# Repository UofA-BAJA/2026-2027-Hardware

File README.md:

# 2026-2027-Hardware

The repository of all hardware for 2026-2027 UofA Baja

Electrical Lead - Graham VanDerBeek

Software Lead - Karsten Yin

#### Projects:

Tachometer -

Speedometer -

Shock Displacement -

Brake Pressure -

GPS -

CVT Temp -

IMU -

Dash - Adam Esch
 HELLO

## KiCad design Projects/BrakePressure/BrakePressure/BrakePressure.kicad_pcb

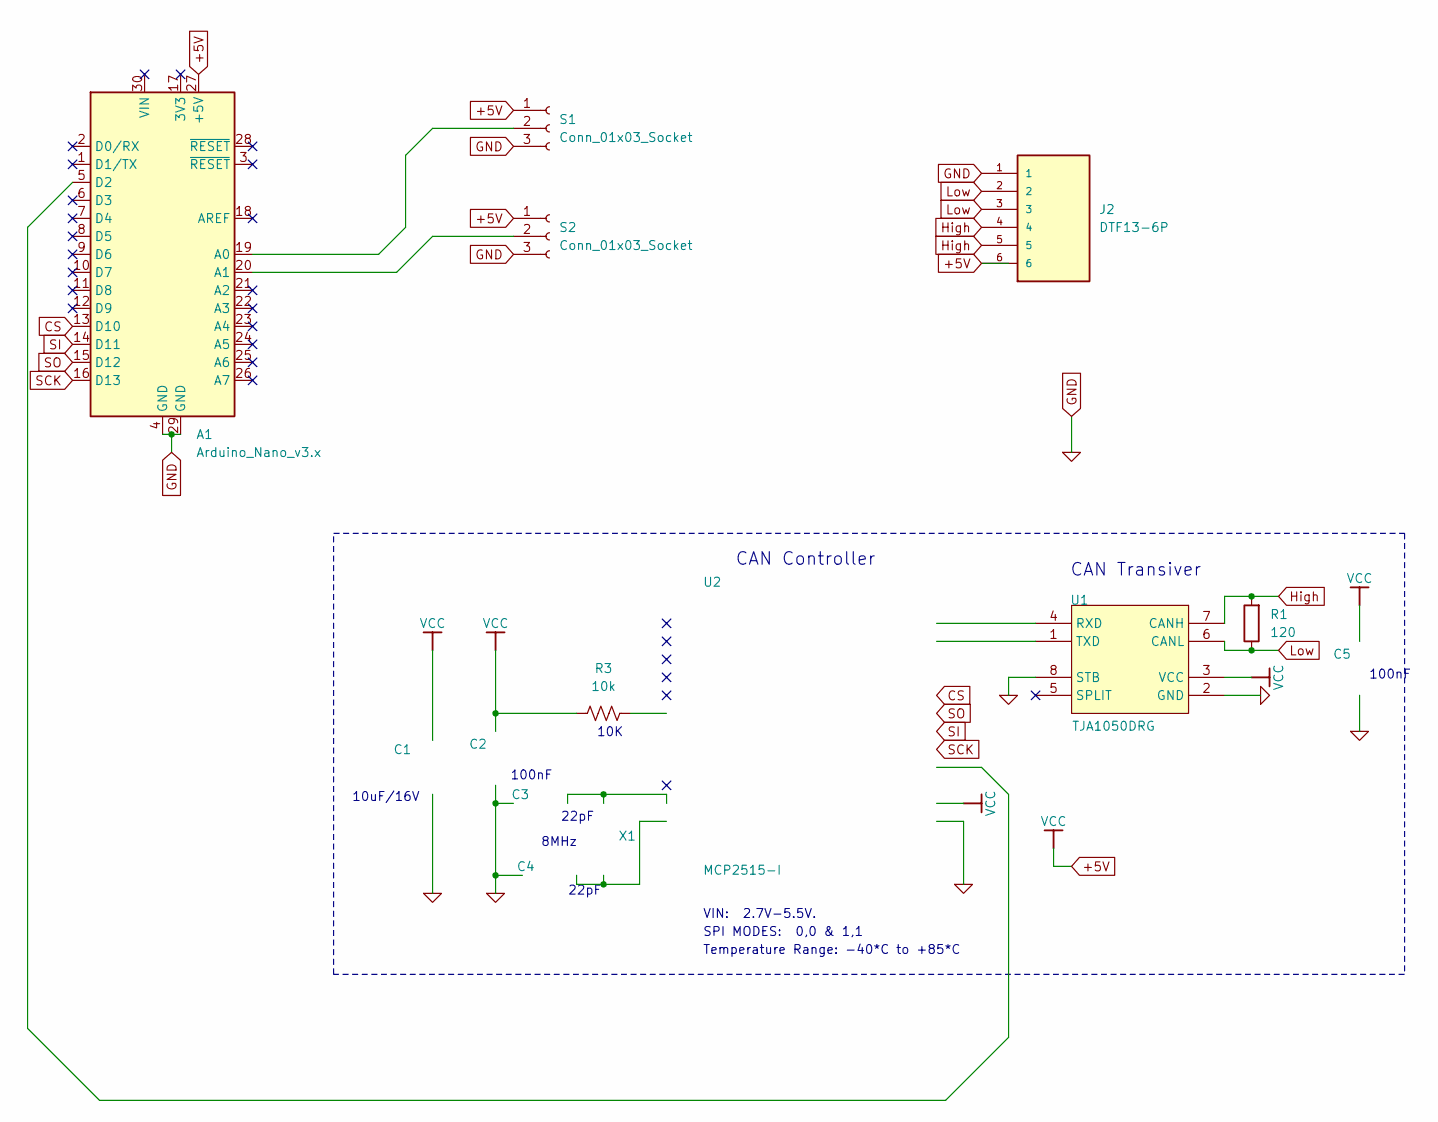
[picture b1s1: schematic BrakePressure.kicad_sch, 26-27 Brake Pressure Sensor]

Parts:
A1: Arduino_Nano_v3.x; Arduino_Nano
C1: 10uF/16V; CP_Radial_Tantal_D5.0mm_P2.50mm
C2, C5: 100nF; CP_Radial_D5.0mm_P2.50mm; PART NUMBER C0603-N.C.
C3, C4: 22pF; CP_Radial_D5.0mm_P2.50mm; PART NUMBER C0603-N.C.
J2: DTF13-6P; TE_DTF13-6P; PARTREV B
R1: 120; R_Axial_DIN0204_L3.6mm_D1.6mm_P7.62mm_Horizontal
R3: 10k; R_Axial_DIN0204_L3.6mm_D1.6mm_P7.62mm_Horizontal
S1, S2: Conn_01x03_Socket; TO-3P-3_Vertical
U1: TJA1050DRG; SOIC-8_5.3x5.3mm_P1.27mm; MANUFACTURER PART TJA1050DRG; LCSC PART NAME TJA1050DRG
U2: MCP2515-I; SOIC-18W_7.5x11.6mm_P1.27mm; MANUFACTURER PART MCP2515-I; JLCPCB PART CLASS Extended Part
X1: 8MHz; Crystal_SMD_HC49-SD

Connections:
+5V: A1.27 (+5V), C1.1, C2.2, C5.2, J2.6, R3.1, S1.1, S2.1, U1.3 (VCC), U2.18 (VDD)
CS: A1.13 (D10), U2.16 (~CS)
GND: A1.4 (GND), A1.29 (GND), C1.2, C2.1, C3.2, C4.2, C5.1, J2.1, S1.3, S2.3, U1.2 (GND), U1.8 (STB), U2.9 (VSS)
High: J2.4, J2.5, R1.2, U1.7 (CANH)
Low: J2.2, J2.3, R1.1, U1.6 (CANL)
unnamed: A1.19 (A0), S1.2
unnamed: A1.20 (A1), S2.2
unnamed: A1.5 (D2), U2.12 (~INT)
unnamed: U1.4 (RXD), U2.2 (RXCAN)
unnamed: U1.1 (TXD), U2.1 (TXCAN)
unnamed: C4.1, U2.8 (OSC1), X1.1
unnamed: C3.1, U2.7 (OSC2), X1.2
unnamed: R3.2, U2.17 (~RESET)
SCK: A1.16 (D13), U2.13 (SCK)
SI: A1.14 (D11), U2.14 (SI)
SO: A1.15 (D12), U2.15 (SO)

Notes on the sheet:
CAN Controller
Temperature Range: -40*C to +85*C
10uF/16V
CAN Transiver
22pF
100nF
10K
VIN: 2.7V-5.5V.
8MHz
SPI MODES: 0,0 & 1,1

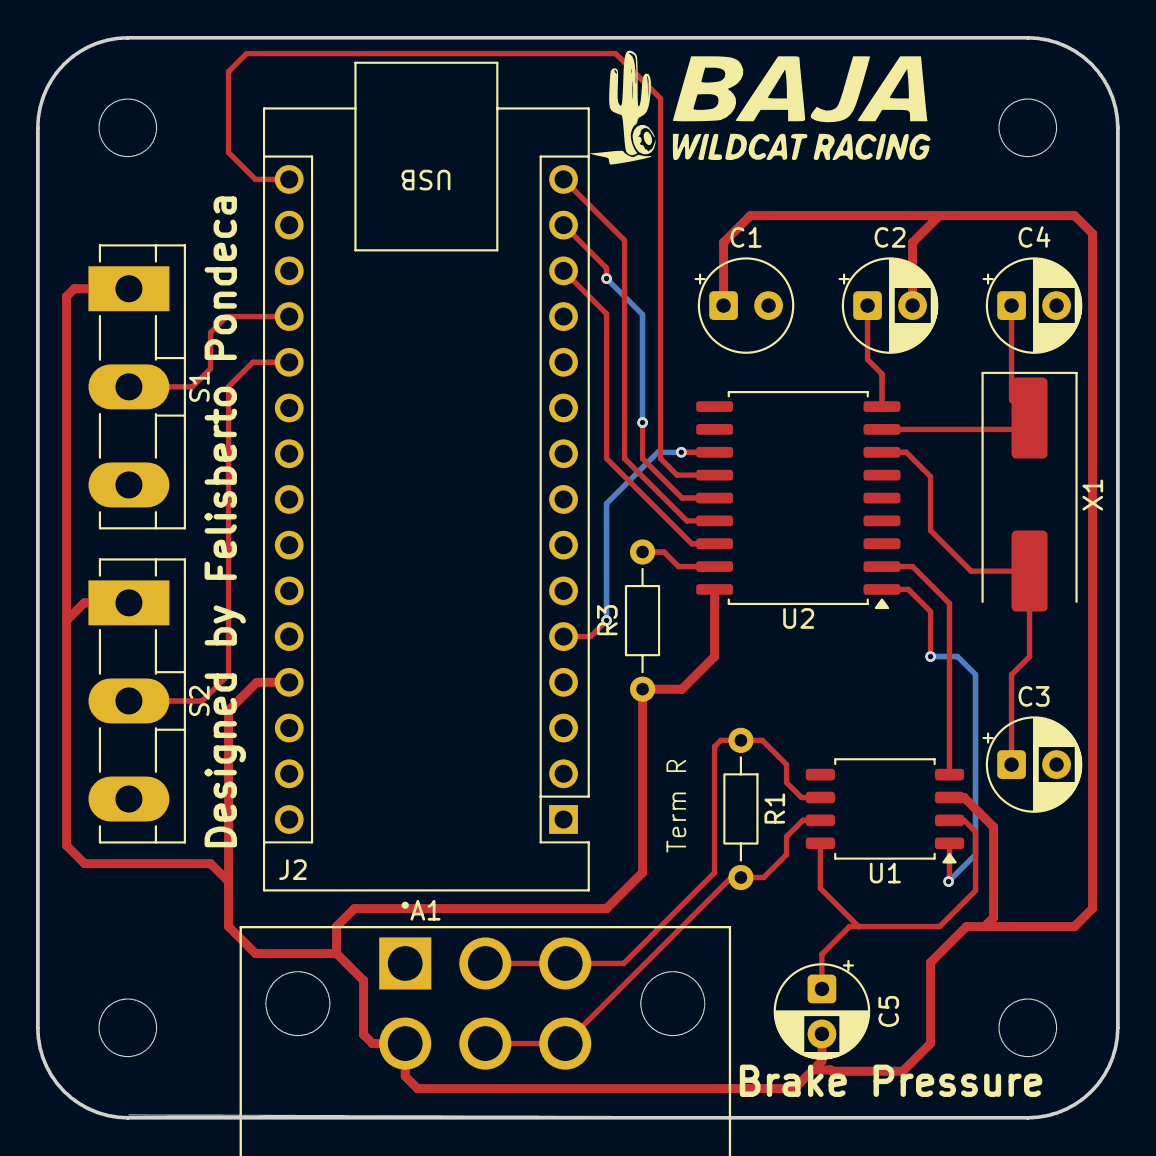
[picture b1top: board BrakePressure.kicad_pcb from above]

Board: 2 copper layers, 60.0 x 60.0 mm, 14 parts (0 on the bottom side), 16 nets.

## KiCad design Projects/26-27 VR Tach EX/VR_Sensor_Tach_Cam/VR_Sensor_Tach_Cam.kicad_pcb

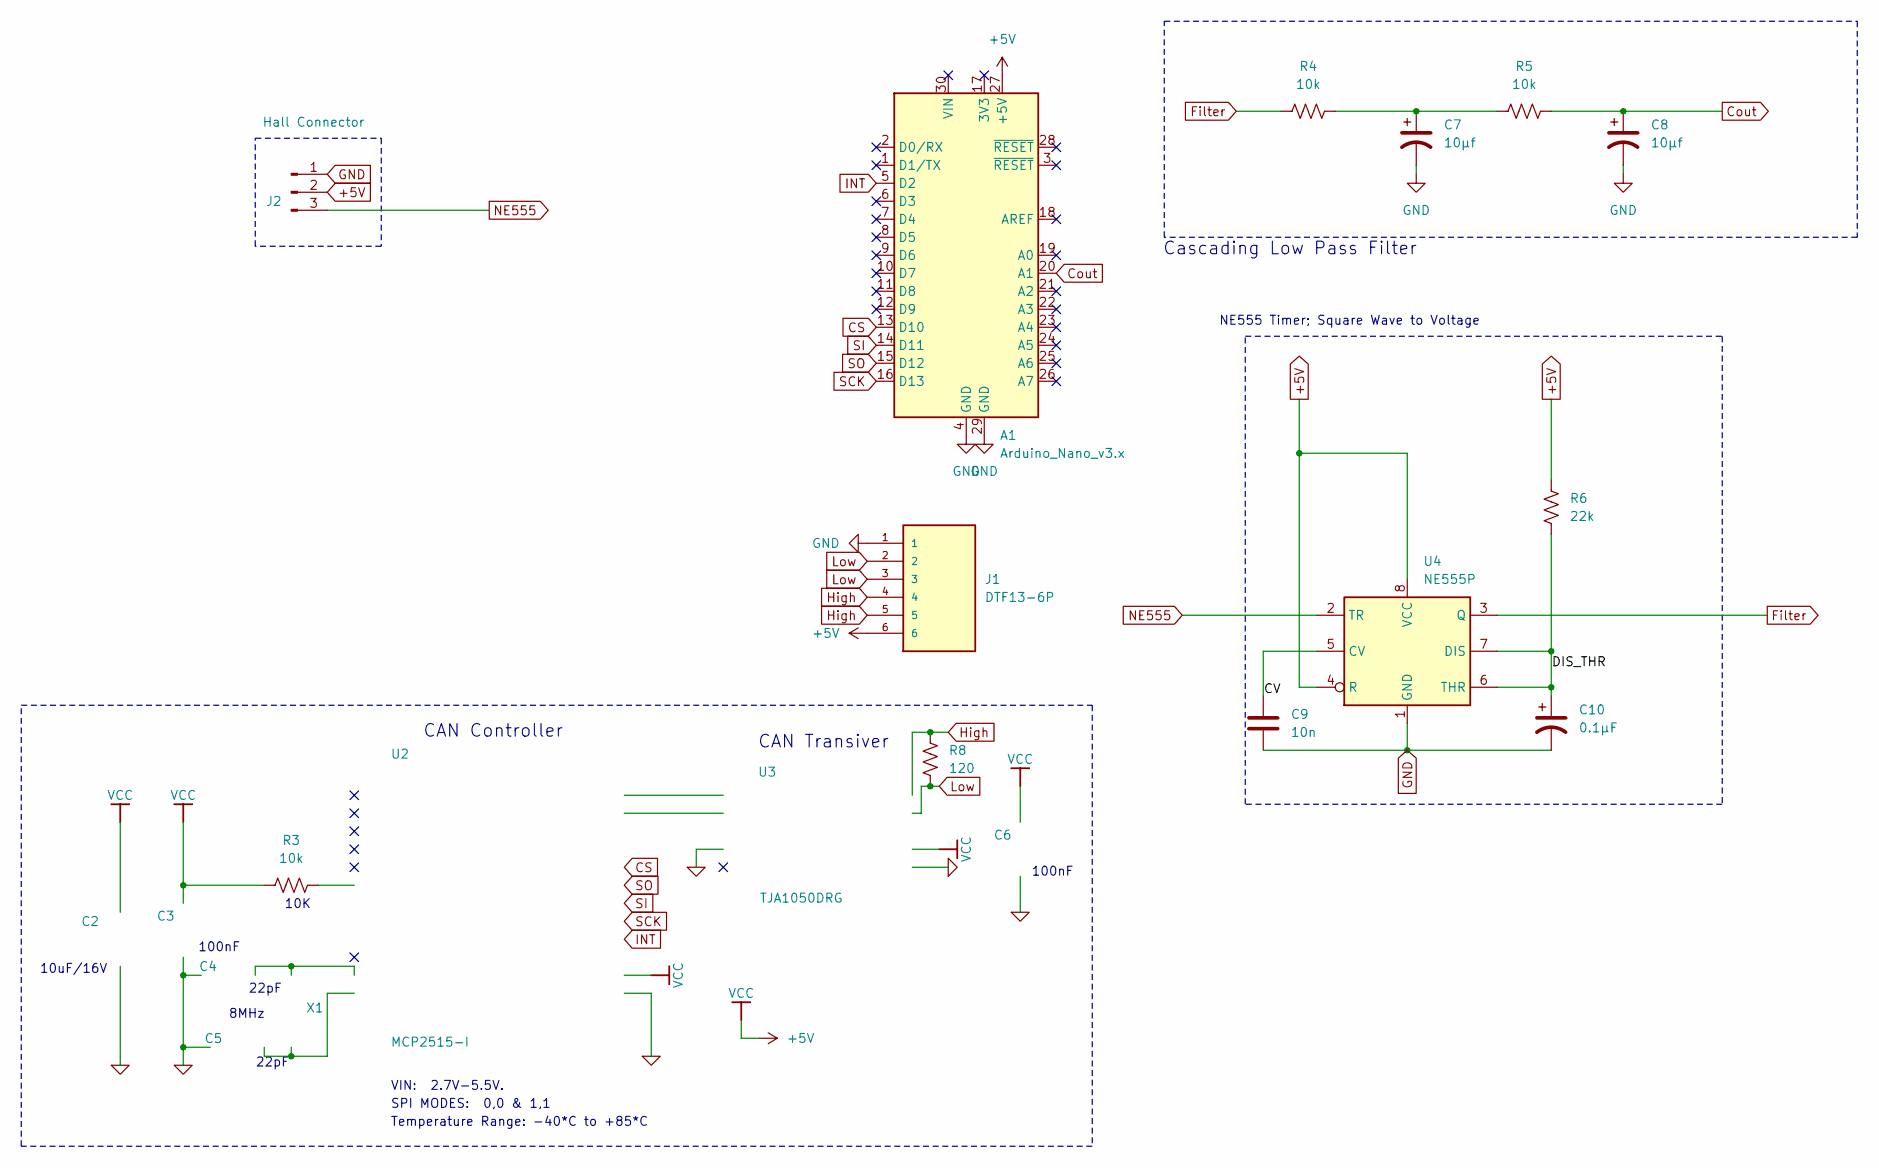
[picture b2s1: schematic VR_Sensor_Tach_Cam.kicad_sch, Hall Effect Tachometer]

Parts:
A1: Arduino_Nano_v3.x; Arduino_Nano
C2: 10uF/16V; CP_Radial_Tantal_D5.0mm_P2.50mm
C3, C6: 100nF; CP_Radial_D5.0mm_P2.50mm; PART NUMBER C0603-N.C.
C4, C5: 22pF; CP_Radial_D5.0mm_P2.50mm; PART NUMBER C0603-N.C.
C7, C8: 10μf; CP_Radial_D5.0mm_P2.50mm
C9: 10n; C_Disc_D3.8mm_W2.6mm_P2.50mm
C10: 0.1µF; CP_Radial_D6.3mm_P2.50mm
J1: DTF13-6P; TE_DTF13-6P; PARTREV B
J2: Hall Connector; SolderWire-2.5sqmm_1x03_P7.2mm_D2.4mm_OD3.6mm
R3, R4, R5: 10k; R_Axial_DIN0207_L6.3mm_D2.5mm_P10.16mm_Horizontal
R6: 22k; R_Axial_DIN0207_L6.3mm_D2.5mm_P10.16mm_Horizontal
R8: 120; R_Axial_DIN0207_L6.3mm_D2.5mm_P10.16mm_Horizontal
U2: MCP2515-I; SOIC-18W_7.5x11.6mm_P1.27mm; MANUFACTURER PART MCP2515-I; JLCPCB PART CLASS Extended Part
U3: TJA1050DRG; SOIC-8_5.3x5.3mm_P1.27mm; MANUFACTURER PART TJA1050DRG; LCSC PART NAME TJA1050DRG
U4: NE555P; DIP-8_W7.62mm
X1: 8MHz; Crystal_SMD_HC49-SD

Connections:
+5V: A1.27 (+5V), C2.1, C3.2, C6.2, J1.6, J2.2, R3.1, R6.1, U2.18 (VDD), U3.3 (VCC), U4.4 (R), U4.8 (VCC)
/CV: C9.2, U4.5 (CV)
/DIS_THR: C10.1, R6.2, U4.6 (THR), U4.7 (DIS)
CS: A1.13 (D10), U2.16 (~CS)
Cout: A1.20 (A1), C8.1, R5.1
Filter: R4.2, U4.3 (Q)
GND: A1.4 (GND), A1.29 (GND), C2.2, C3.1, C4.2, C5.2, C6.1, C7.2, C8.2, C9.1, C10.2, J1.1, J2.1, U2.9 (VSS), U3.2 (GND), U3.8 (STB), U4.1 (GND)
High: J1.4, J1.5, R8.1, U3.7 (CANH); also elsewhere on the board
INT: A1.5 (D2), U2.12 (~INT)
Low: J1.2, J1.3, R8.2, U3.6 (CANL); also elsewhere on the board
NE555: J2.3, U4.2 (TR)
unnamed: C7.1, R4.1, R5.2
unnamed: C5.1, U2.8 (OSC1), X1.1
unnamed: C4.1, U2.7 (OSC2), X1.2
unnamed: U2.2 (RXCAN), U3.4 (RXD)
unnamed: U2.1 (TXCAN), U3.1 (TXD)
unnamed: R3.2, U2.17 (~RESET)
SCK: A1.16 (D13), U2.13 (SCK)
SI: A1.14 (D11), U2.14 (SI)
SO: A1.15 (D12), U2.15 (SO)

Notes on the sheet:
VIN: 2.7V-5.5V.
8MHz
Cascading Low Pass Filter
10uF/16V
100nF
SPI MODES: 0,0 & 1,1
CAN Controller
CAN Transiver
10K
22pF
NE555 Timer; Square Wave to Voltage
Temperature Range: -40*C to +85*C

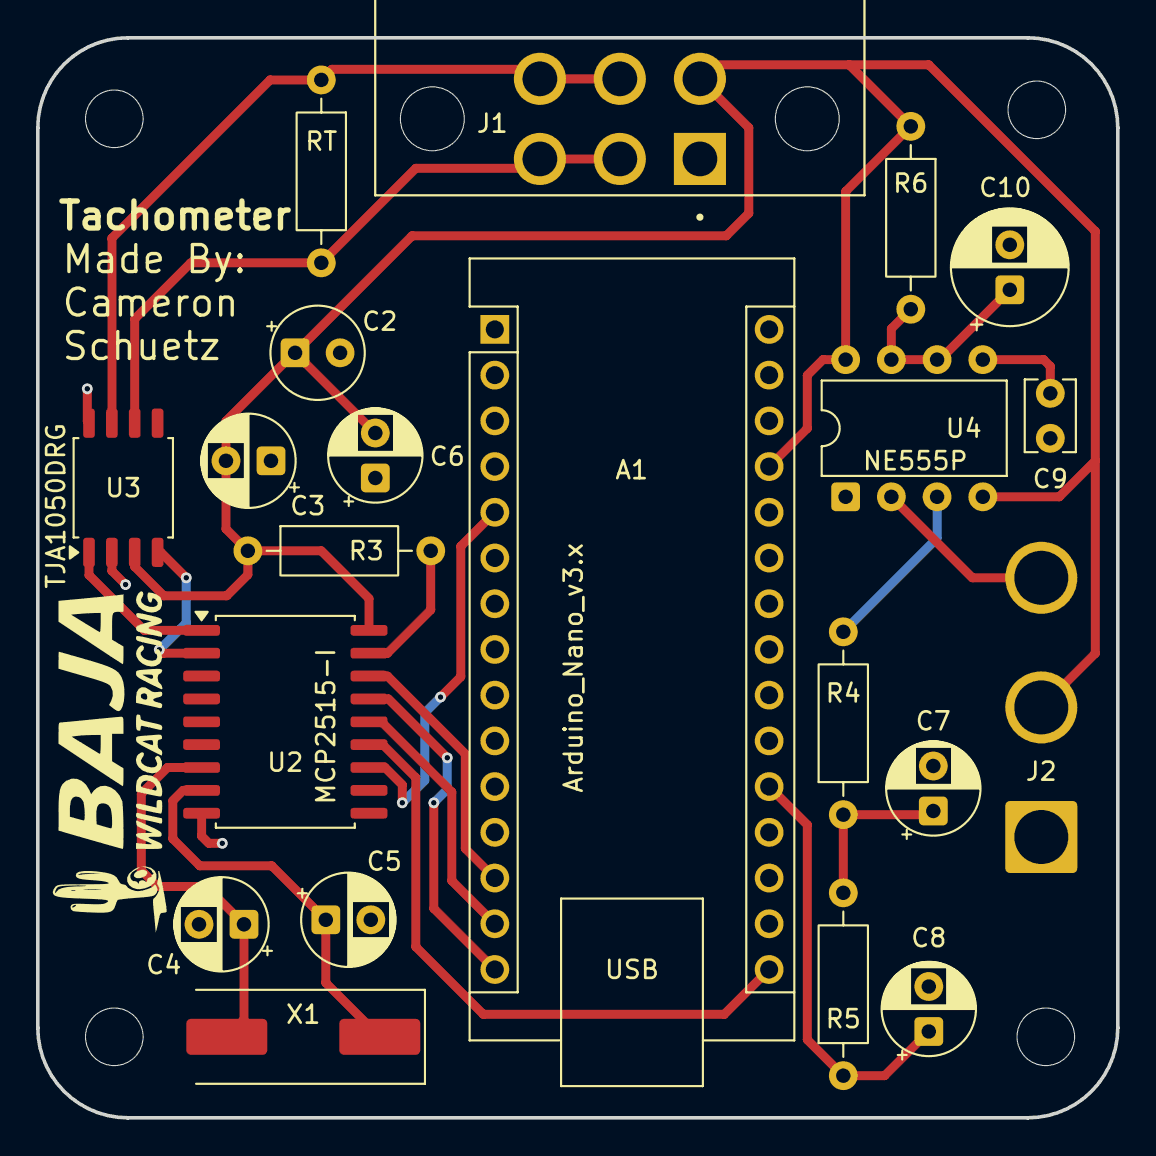
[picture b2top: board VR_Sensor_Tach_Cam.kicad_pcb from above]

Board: 2 copper layers, 60.0 x 60.0 mm, 21 parts (0 on the bottom side), 20 nets.

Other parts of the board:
RT: 120; R_Axial_DIN0207_L6.3mm_D2.5mm_P10.16mm_Horizontal

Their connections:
High: RT.1; also elsewhere on the board
Low: RT.2; also elsewhere on the board

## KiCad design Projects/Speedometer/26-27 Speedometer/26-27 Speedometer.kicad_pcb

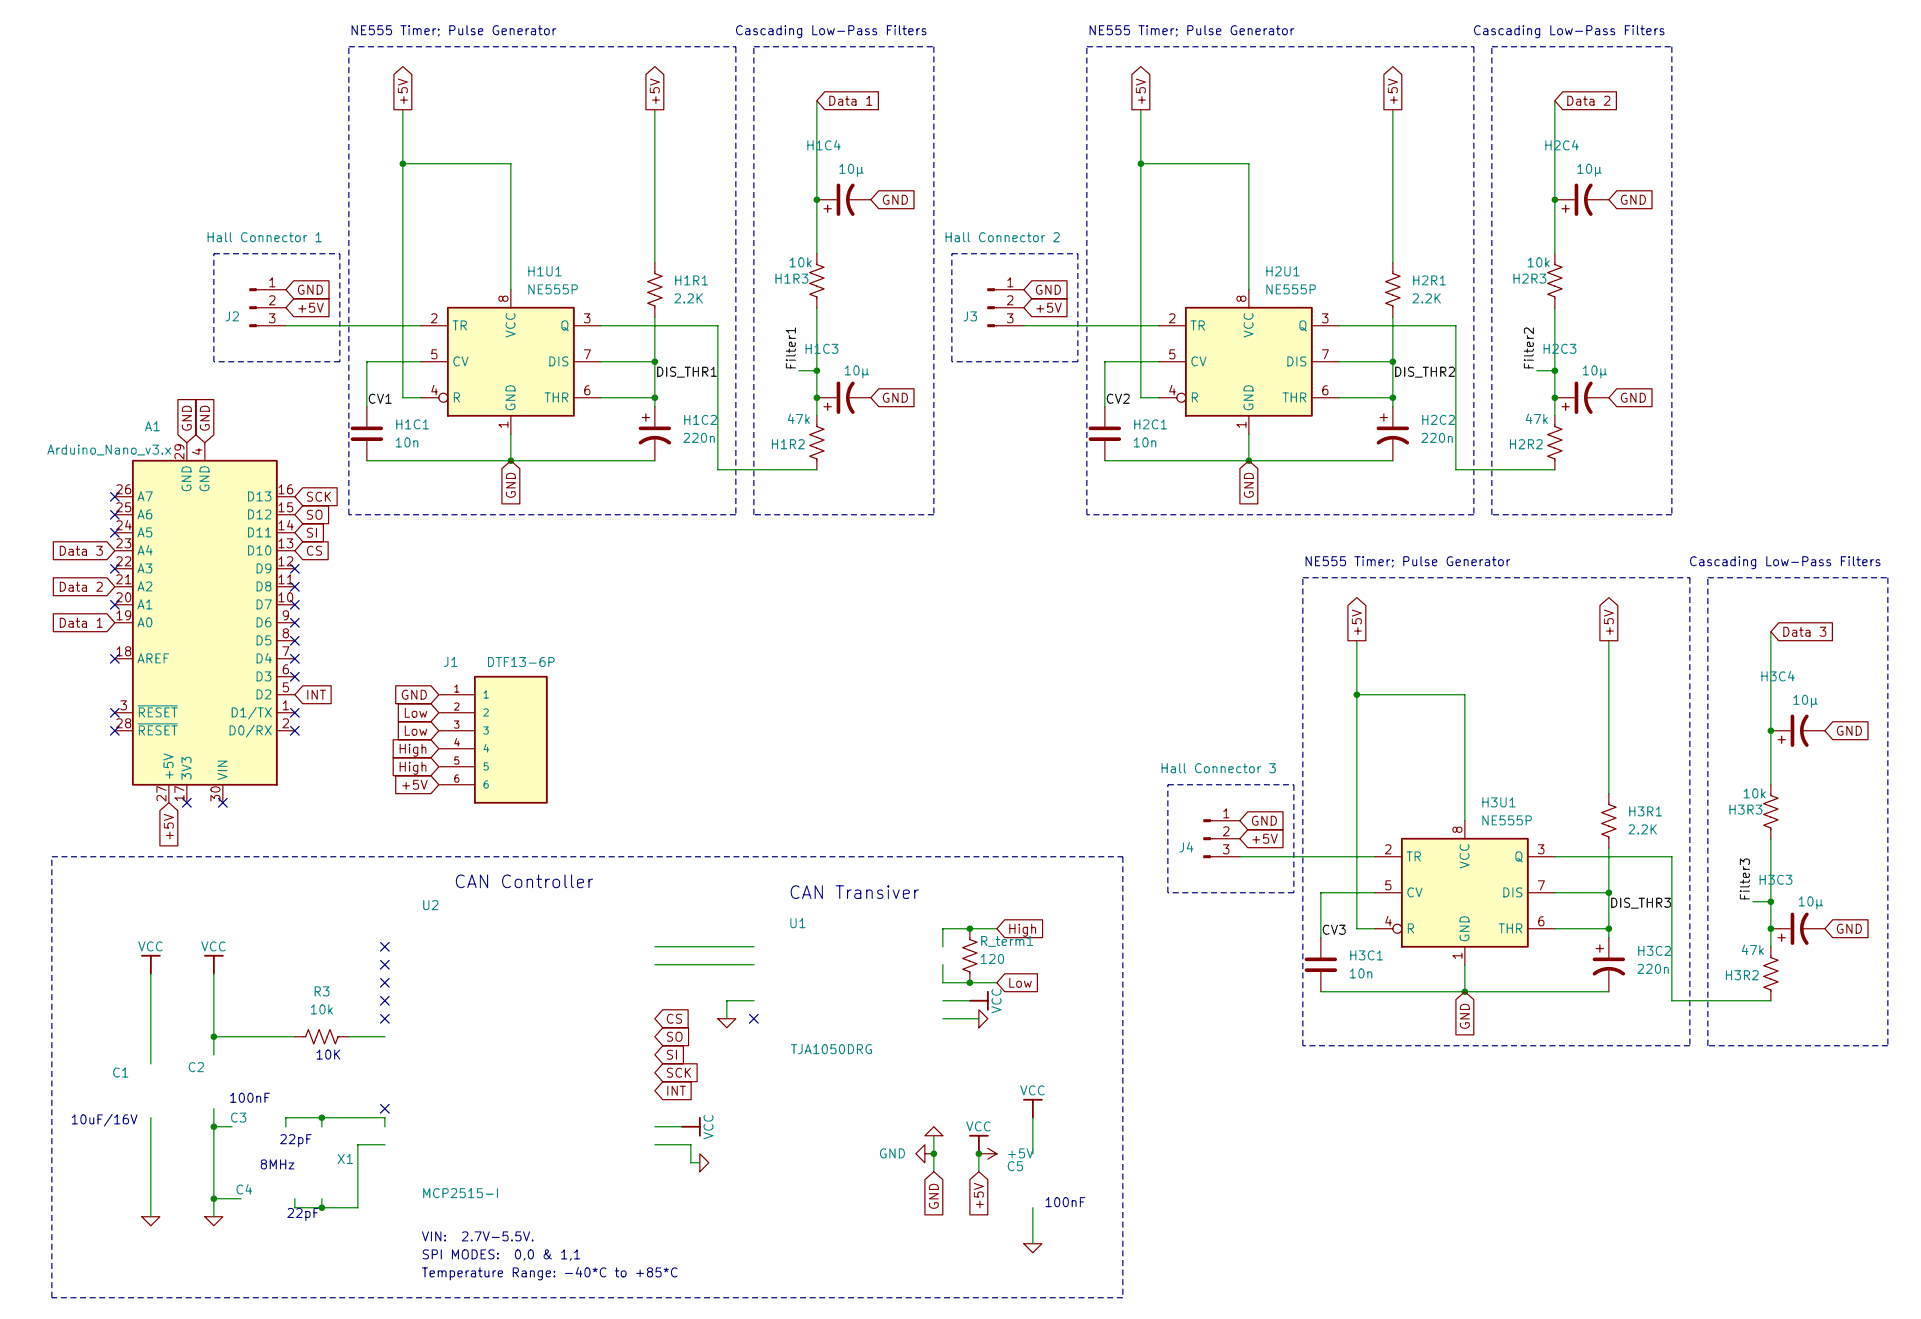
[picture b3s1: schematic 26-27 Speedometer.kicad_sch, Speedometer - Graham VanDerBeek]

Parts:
A1: Arduino_Nano_v3.x; Arduino_Nano
C1: 10uF/16V; CP_Radial_Tantal_D5.0mm_P2.50mm
C2, C5: 100nF; CP_Radial_D5.0mm_P2.50mm; PART NUMBER C0603-N.C.
C3, C4: 22pF; CP_Radial_D5.0mm_P2.50mm; PART NUMBER C0603-N.C.
H1C1, H2C1, H3C1: 10n; C_Disc_D3.8mm_W2.6mm_P2.50mm
H1C2, H2C2, H3C2: 220n; CP_Radial_D6.3mm_P2.50mm
H1C3, H1C4, H2C3, H2C4, H3C3, H3C4: 10µ; CP_Radial_D4.0mm_P2.00mm
H1R1, H2R1, H3R1: 2.2K; R_Axial_DIN0207_L6.3mm_D2.5mm_P10.16mm_Horizontal
H1R2, H2R2, H3R2: 47k; R_Axial_DIN0207_L6.3mm_D2.5mm_P10.16mm_Horizontal
H1R3, H2R3, H3R3: 10k; R_Axial_DIN0207_L6.3mm_D2.5mm_P10.16mm_Horizontal
H1U1, H2U1, H3U1: NE555P; DIP-8_W7.62mm
J1: DTF13-6P; TE_DTF13-6P; PARTREV B
J2: Hall Connector 1; SolderWire-2.5sqmm_1x03_P7.2mm_D2.4mm_OD3.6mm
J3: Hall Connector 2; SolderWire-2.5sqmm_1x03_P7.2mm_D2.4mm_OD3.6mm
J4: Hall Connector 3; SolderWire-2.5sqmm_1x03_P7.2mm_D2.4mm_OD3.6mm
R3: 10k; R_Axial_DIN0207_L6.3mm_D2.5mm_P10.16mm_Horizontal
R_term1: 120; R_Axial_DIN0207_L6.3mm_D2.5mm_P10.16mm_Horizontal
U1: TJA1050DRG; SOIC-8_5.3x5.3mm_P1.27mm; MANUFACTURER PART TJA1050DRG; LCSC PART NAME TJA1050DRG
U2: MCP2515-I; SOIC-18W_7.5x11.6mm_P1.27mm; MANUFACTURER PART MCP2515-I; JLCPCB PART CLASS Extended Part
X1: 8MHz; Crystal_SMD_HC49-SD

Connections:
+5V: A1.27 (+5V), C1.1, C2.2, C5.2, H1R1.1, H1U1.4 (R), H1U1.8 (VCC), H2R1.1, H2U1.4 (R), H2U1.8 (VCC), H3R1.1, H3U1.4 (R), H3U1.8 (VCC), J1.6, J2.2, J3.2, J4.2, R3.1, U1.3 (VCC), U2.18 (VDD)
/CV1: H1C1.2, H1U1.5 (CV)
/CV2: H2C1.2, H2U1.5 (CV)
/CV3: H3C1.2, H3U1.5 (CV)
/DIS_THR1: H1C2.1, H1R1.2, H1U1.6 (THR), H1U1.7 (DIS)
/DIS_THR2: H2C2.1, H2R1.2, H2U1.6 (THR), H2U1.7 (DIS)
/DIS_THR3: H3C2.1, H3R1.2, H3U1.6 (THR), H3U1.7 (DIS)
/Filter1: H1C3.1, H1R2.2, H1R3.1
/Filter2: H2C3.1, H2R2.2, H2R3.1
/Filter3: H3C3.1, H3R2.2, H3R3.1
CS: A1.13 (D10), U2.16 (~CS)
Data 1: A1.19 (A0), H1C4.1, H1R3.2
Data 2: A1.21 (A2), H2C4.1, H2R3.2
Data 3: A1.23 (A4), H3C4.1, H3R3.2
GND: A1.4 (GND), A1.29 (GND), C1.2, C2.1, C3.2, C4.2, C5.1, H1C1.1, H1C2.2, H1C3.2, H1C4.2, H1U1.1 (GND), H2C1.1, H2C2.2, H2C3.2, H2C4.2, H2U1.1 (GND), H3C1.1, H3C2.2, H3C3.2, H3C4.2, H3U1.1 (GND), J1.1, J2.1, J3.1, J4.1, U1.2 (GND), U1.8 (STB), U2.9 (VSS)
High: J1.4, J1.5, R_term1.1, U1.7 (CANH)
INT: A1.5 (D2), U2.12 (~INT)
Low: J1.2, J1.3, R_term1.2, U1.6 (CANL)
unnamed: H1R2.1, H1U1.3 (Q)
unnamed: H1U1.2 (TR), J2.3
unnamed: H2R2.1, H2U1.3 (Q)
unnamed: H2U1.2 (TR), J3.3
unnamed: H3R2.1, H3U1.3 (Q)
unnamed: H3U1.2 (TR), J4.3
unnamed: U1.4 (RXD), U2.2 (RXCAN)
unnamed: U1.1 (TXD), U2.1 (TXCAN)
unnamed: C4.1, U2.8 (OSC1), X1.1
unnamed: C3.1, U2.7 (OSC2), X1.2
unnamed: R3.2, U2.17 (~RESET)
SCK: A1.16 (D13), U2.13 (SCK)
SI: A1.14 (D11), U2.14 (SI)
SO: A1.15 (D12), U2.15 (SO)

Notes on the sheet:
Cascading Low-Pass Filters
SPI MODES: 0,0 & 1,1
8MHz
Temperature Range: -40*C to +85*C
10uF/16V
VIN: 2.7V-5.5V.
NE555 Timer; Pulse Generator
CAN Transiver
100nF
22pF
CAN Controller
10K

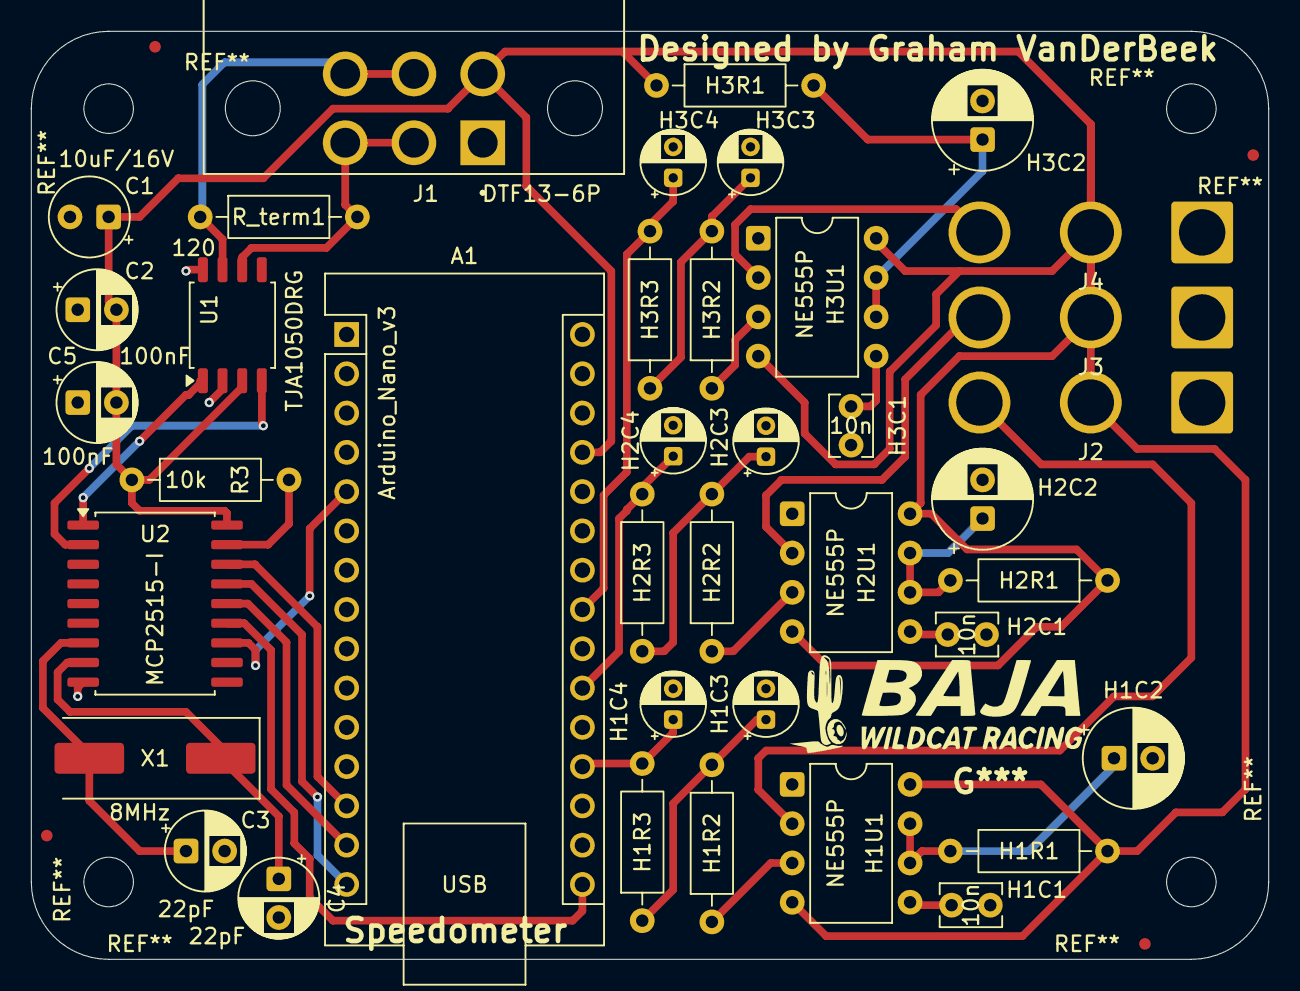
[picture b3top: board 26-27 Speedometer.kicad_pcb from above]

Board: 2 copper layers, 80.0 x 60.0 mm, 39 parts (0 on the bottom side), 32 nets.

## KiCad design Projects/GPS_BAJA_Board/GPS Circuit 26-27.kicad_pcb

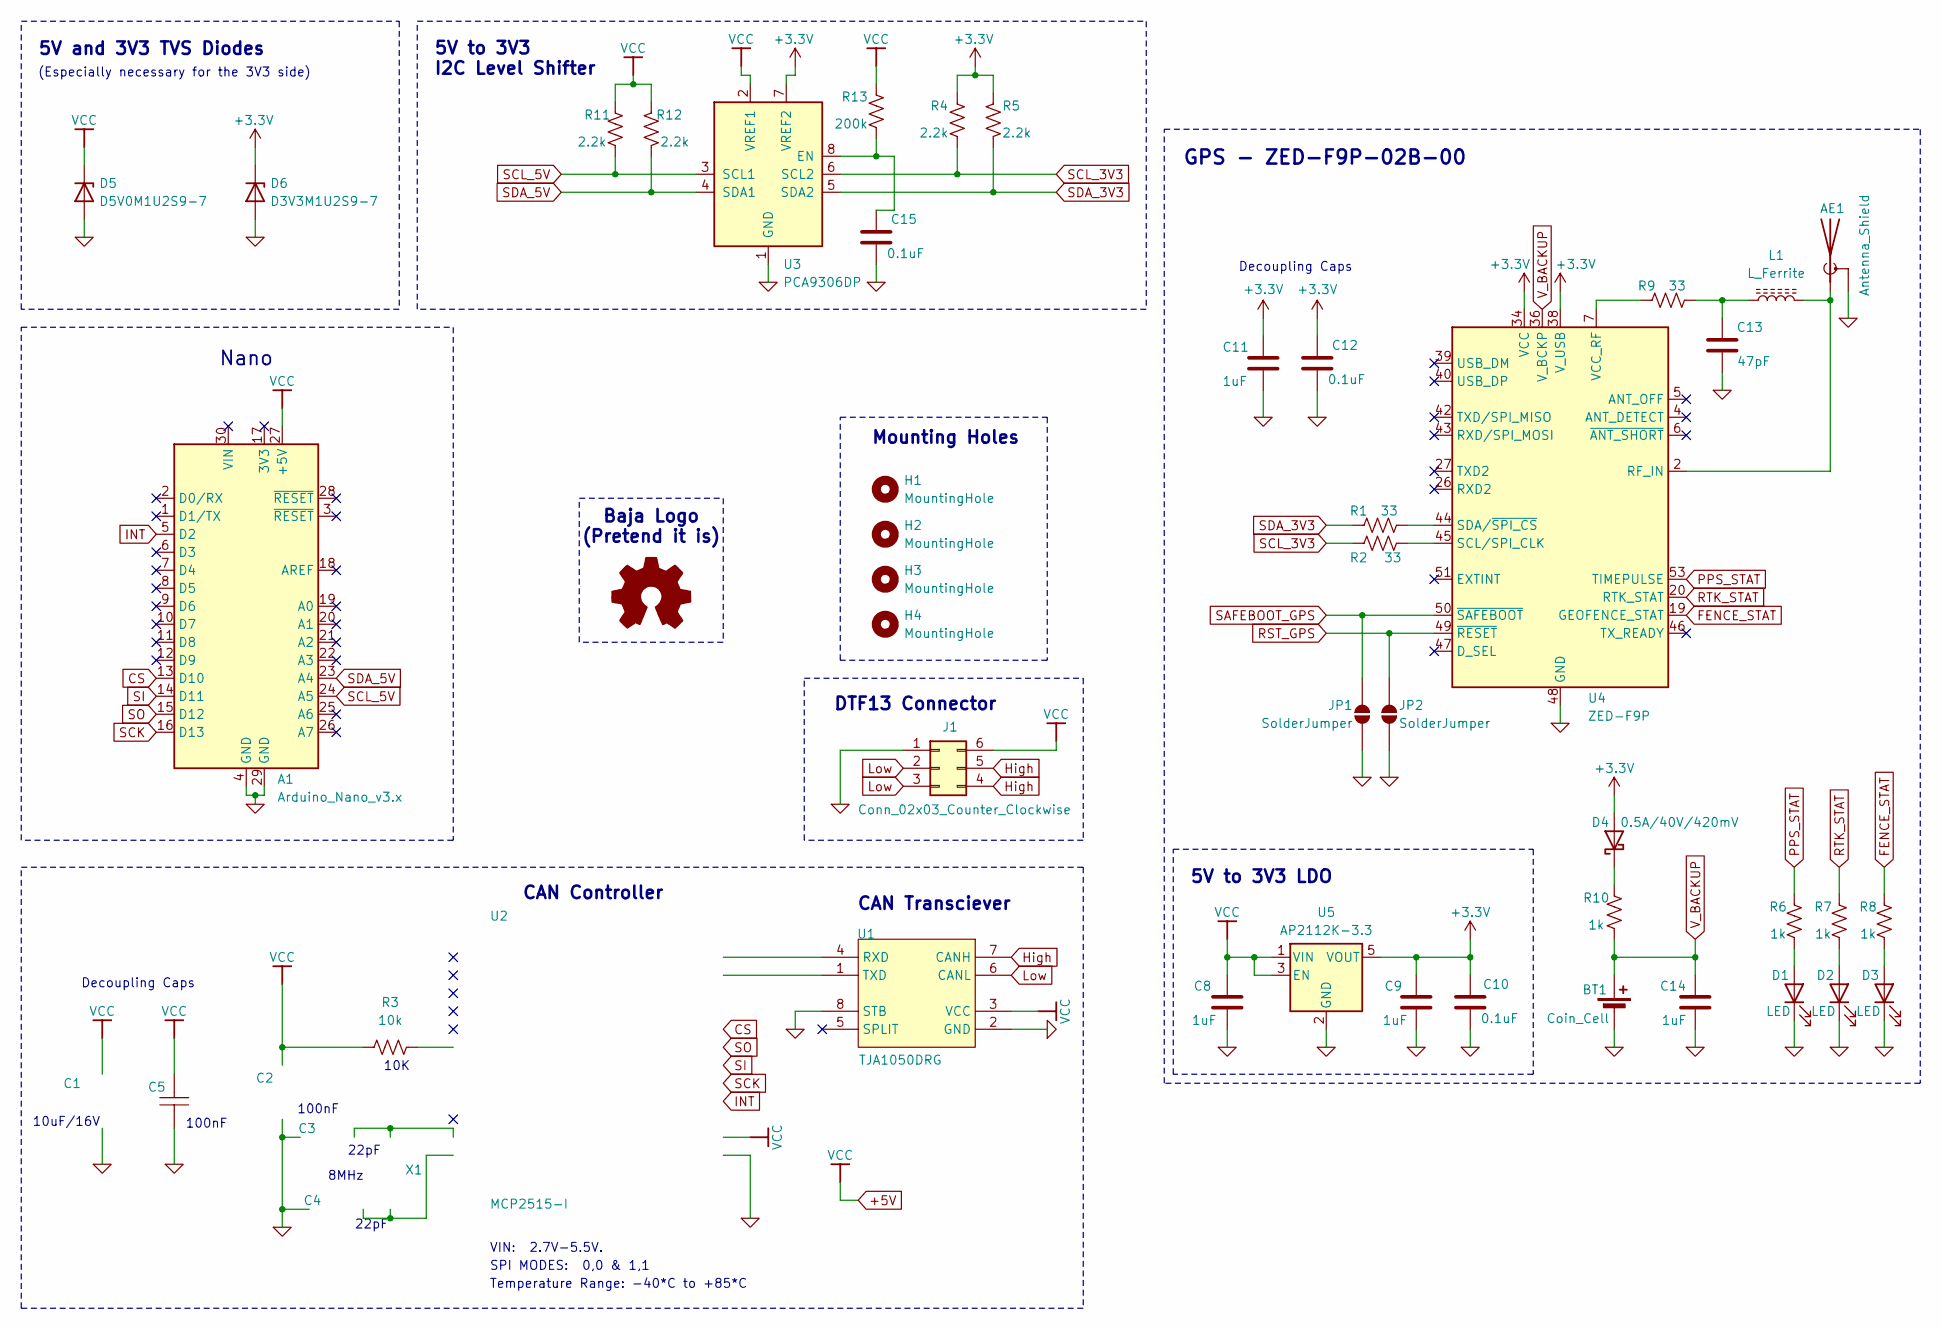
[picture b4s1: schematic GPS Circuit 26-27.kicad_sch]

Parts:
A1: Arduino_Nano_v3.x; Arduino_Nano
AE1: Antenna_Shield; U.FL_Hirose_U.FL-R-SMT-1_Vertical
BT1: Coin_Cell; BatteryHolder_Seiko_MS621F
C1: 10uF/16V; CP_Radial_Tantal_D5.0mm_P2.50mm
C2, C5: 100nF; CP_Radial_D5.0mm_P2.50mm; PART NUMBER C0603-N.C.
C3, C4: 22pF; CP_Radial_D5.0mm_P2.50mm; PART NUMBER C0603-N.C.
C8, C9, C11, C14: 1uF; C_0603_1608Metric
C10, C12, C15: 0.1uF; C_0603_1608Metric
C13: 47pF; C_0603_1608Metric
D1, D2, D3: LED; LED_0603_1608Metric
D4: 0.5A/40V/420mV; D_SOD-123
D5: D5V0M1U2S9-7; Nexperia_DSN1608-2_1.6x0.8mm
D6: D3V3M1U2S9-7; Nexperia_DSN1608-2_1.6x0.8mm
H1, H2, H3, H4: MountingHole; MountingHole_3.2mm_M3
J1: Conn_02x03_Counter_Clockwise; TE_DTF13-6P
JP1, JP2: SolderJumper; SolderJumper-2_P1.3mm_Open_TrianglePad1.0x1.5mm
L1: L_Ferrite; L_Eaton_MCL2012V1
Logo1: Logo_Open_Hardware_Small; Baja Logo
R1, R2, R9: 33; R_0603_1608Metric
R3: 10k; R_Axial_DIN0207_L6.3mm_D2.5mm_P5.08mm_Vertical
R4, R5, R11, R12: 2.2k; R_0603_1608Metric
R6, R7, R8, R10: 1k; R_0603_1608Metric
R13: 200k; R_0603_1608Metric
U1: TJA1050DRG; SOIC-8_5.3x5.3mm_P1.27mm; MANUFACTURER PART TJA1050DRG; LCSC PART NAME TJA1050DRG
U2: MCP2515-I; SOIC-18W_7.5x11.6mm_P1.27mm; MANUFACTURER PART MCP2515-I; JLCPCB PART CLASS Extended Part
U3: PCA9306DP; TSSOP-8_3x3mm_P0.65mm
U4: ZED-F9P; ublox_ZED
U5: AP2112K-3.3; SOT-23-5
X1: 8MHz; Crystal_SMD_HC49-SD

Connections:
0: A1.4 (GND), A1.29 (GND), AE1.2 (Shield), BT1.2 (-), C1.2, C2.1, C3.2, C4.2, C5.1, C8.2, C9.2, C10.1, C11.2, C12.1, C13.1, C14.2, C15.1, D1.1 (K), D2.1 (K), D3.1 (K), D5.2 (A), D6.2 (A), J1.1, JP1.1 (A), JP2.1 (A), U1.2 (GND), U1.8 (STB), U2.9 (VSS), U3.1 (GND), U4.1 (GND), U4.3 (GND), U4.12 (GND), U4.14 (GND), U4.32 (GND), U4.37 (GND), U4.41 (GND), U4.48 (GND), U4.55 (GND), U5.2 (GND); also elsewhere on the board
+3.3V: C9.1, C10.2, C11.1, C12.2, D4.2 (A), D6.1 (K), R4.2, R5.2, U3.7 (VREF2), U4.33 (VCC), U4.34 (VCC), U4.38 (V_USB), U5.5 (VOUT)
+5V: A1.27 (+5V), C1.1, C2.2, C5.2, C8.1, D5.1 (K), J1.6, R3.1, R11.2, R12.2, R13.2, U1.3 (VCC), U2.18 (VDD), U3.2 (VREF1), U5.1 (VIN), U5.3 (EN); also elsewhere on the board
CS: A1.13 (D10), U2.16 (~CS)
FENCE_STAT: R8.2, U4.19 (GEOFENCE_STAT)
High: J1.4, J1.5, U1.7 (CANH)
INT: A1.5 (D2), U2.12 (~INT)
Low: J1.2, J1.3, U1.6 (CANL)
unnamed: AE1.1 (A), L1.2, U4.2 (RF_IN)
unnamed: C13.2, L1.1, R9.1
unnamed: D1.2 (A), R6.1
unnamed: D2.2 (A), R7.1
unnamed: D3.2 (A), R8.1
unnamed: D4.1 (K), R10.2
unnamed: U1.4 (RXD), U2.2 (RXCAN)
unnamed: U1.1 (TXD), U2.1 (TXCAN)
unnamed: C4.1, U2.8 (OSC1), X1.1
unnamed: C3.1, U2.7 (OSC2), X1.2
unnamed: R3.2, U2.17 (~RESET)
unnamed: C15.2, R13.1, U3.8 (EN)
unnamed: R2.2, U4.45 (SCL/SPI_CLK)
unnamed: R1.1, U4.44 (SDA/~SPI_CS)
unnamed: R9.2, U4.7 (VCC_RF)
PPS_STAT: R6.2, U4.53 (TIMEPULSE)
RST_GPS: JP2.2 (B), U4.49 (~RESET)
RTK_STAT: R7.2, U4.20 (RTK_STAT)
SAFEBOOT_GPS: JP1.2 (B), U4.50 (~SAFEBOOT)
SCK: A1.16 (D13), U2.13 (SCK)
SCL_3V3: R2.1, R4.1, U3.6 (SCL2)
SCL_5V: A1.24 (A5), R11.1, U3.3 (SCL1)
SDA_3V3: R1.2, R5.1, U3.5 (SDA2)
SDA_5V: A1.23 (A4), R12.1, U3.4 (SDA1)
SI: A1.14 (D11), U2.14 (SI)
SO: A1.15 (D12), U2.15 (SO)
V_BACKUP: BT1.1 (+), C14.1, R10.1, U4.36 (V_BCKP)

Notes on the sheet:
GPS - ZED-F9P-02B-00
10K
Decoupling Caps
Temperature Range: -40*C to +85*C
5V to 3V3 I2C Level Shifter
22pF
100nF
CAN Controller
8MHz
Nano
(Especially necessary for the 3V3 side)
DTF13 Connector
5V to 3V3 LDO
SPI MODES: 0,0 & 1,1
Baja Logo (Pretend it is)
CAN Transciever
10uF/16V
5V and 3V3 TVS Diodes
Mounting Holes
VIN: 2.7V-5.5V.

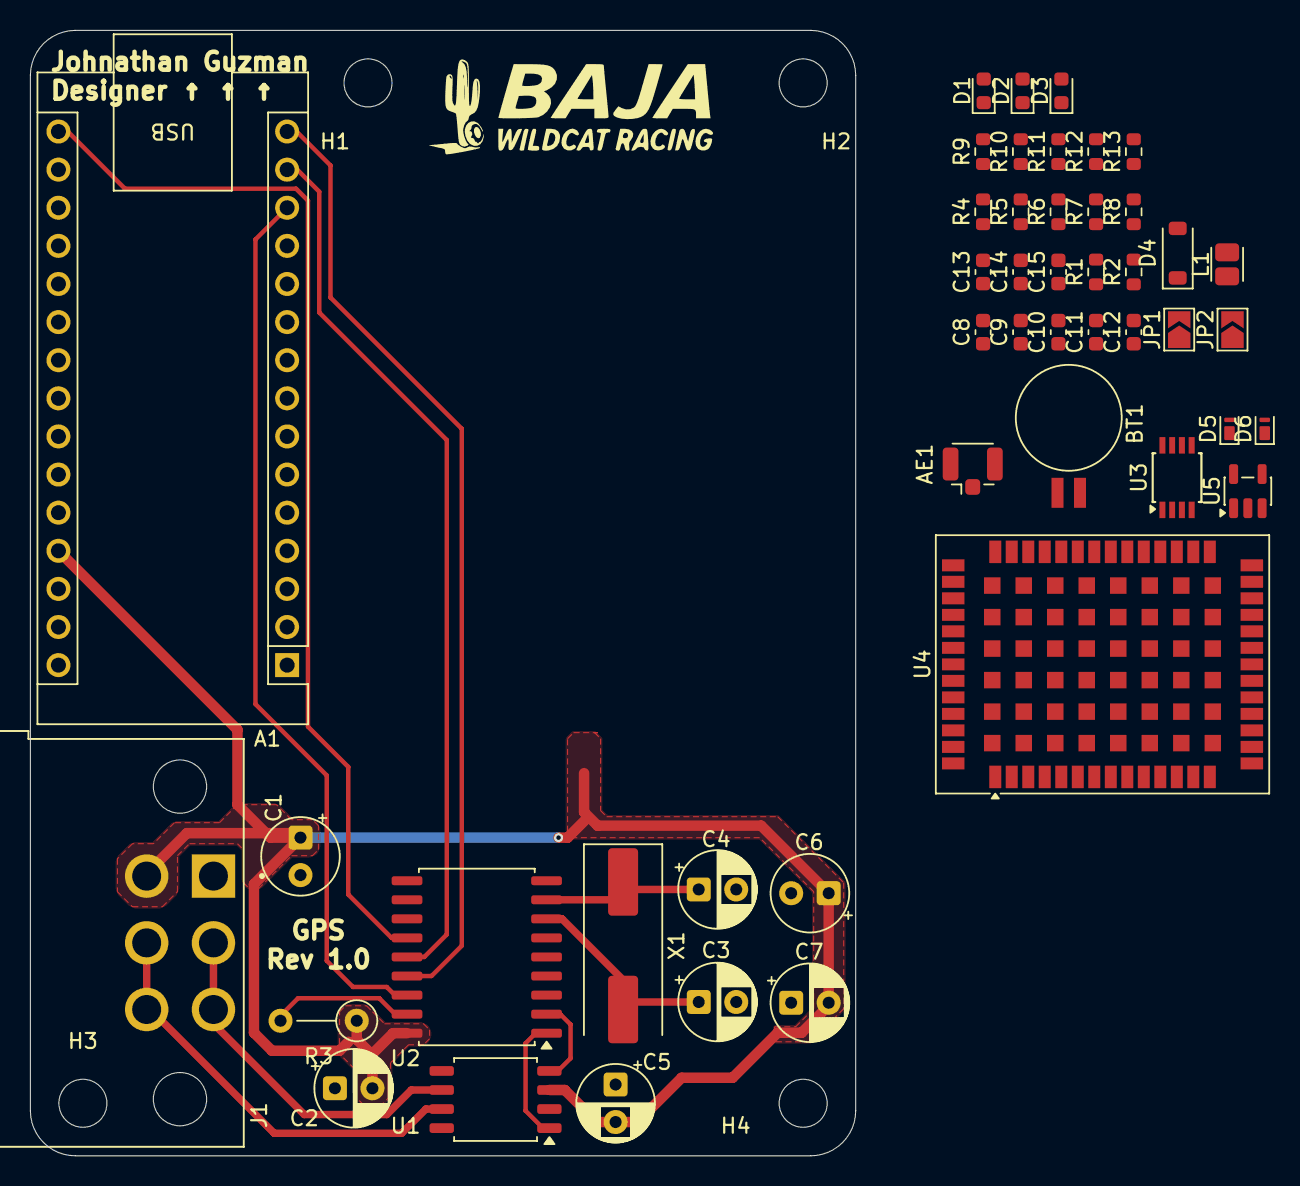
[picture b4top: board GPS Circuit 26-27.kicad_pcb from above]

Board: 2 copper layers, 55.0 x 75.0 mm, 51 parts (0 on the bottom side), 35 nets.

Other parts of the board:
C6: 10uF/16V; CP_Radial_Tantal_D5.0mm_P2.50mm
C7: 100nF; CP_Radial_D5.0mm_P2.50mm

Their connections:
0: C6.2, C7.1; also elsewhere on the board
+5V: C6.1, C7.2; also elsewhere on the board
